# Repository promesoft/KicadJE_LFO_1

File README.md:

# Johansen Engineering KiCadJE_LFO_1.2 (Rev B)

Analogue LFO - minor adjustments - new jacks (PJ321 -> pj324) - remove Sine Adj

555 Based LFO - minor adjustments - new jacks (PJ321 -> pj324) - remove XXX

NAND - Footprint adj

# Purpose
Fix issues with RevA

## 555 LFO
+/- 10V LFO Square, Triangle, Sine

2 frequency ranges

## LFO
+/- 10V LFO Square, Triangle, Sine

## NAND
NOT Gate (pull dn) - NAND Gate (both pull up) - AND Gate (both pull up)

0-10V output - CMOS input

## D-Flip Flop
0-10V output - CMOS input

## MMX
+-10V Input/output - DC couple

Top - 3 input mixer with phase reversal

Bottom - 3 mult output with phase reversal - uses mixer output as input if not applied to mult input

# Status - In the mail
## Initial 
| Stage  | Detail | Status |
| ------------- | ------------- | ------------- |
| create material  | sch/pcb | OK  |
| | gerber | OK |
| production  |   | OK |
|  | produced | Yes |
|  | delivered | OK |

## Preliminary validation
| Test  | Detail | Status |
| ------------- | ------------- | ------------- |
| Initial Inspection | | OK |
| Initial Technical Test | LFO555 |  |
| | | PJ321 should be 1 mm further from the front, center tap works - minor footprint twist in pj324|
| Initial Technical Test | NAND |  |
| | | cut power plane and add 20k across to fix not blowing other units due to hard pull up on tip.
| Initial Product Test | LFO |  |
| Initial Product Test | LFO555 | Sine and Tri not working - needs ac coupling from square - needs dc compensation |
| Initial Product Test | MMX2 |   |
| Initial Product Test | NAND | Now working with 4093 - needs pull up resistors and I/O protection |
| Initial Product Test | FlipFlop |  |

## Secondary validation
| Test  | Detail | Status |
| ------------- | ------------- |------------- |
| Product Test | LFO | |
| Product Test | LFO555 | working right - tri and sine needs tweaking of waveforms |
| Product Test | MMX2 |  |
| Product Test | NAND | working - see issues |
| Product Test | FlipFlop | Working as intended except for LED's |
| Quality | LFO | |
| Quality | LFO555 | |
| Quality | MMX2 | |
| Quality | NAND |  |
| Quality | FlipFlop | |
| Long Term Product Test |  |  |
| Power Draw |  | 

## Errata
### Errata - LFO

### Errata - LFO555

### Errata - MMX2

### Errata - Flip-Flop

### Errata - NAND
Hard pull up to 12 can fry other units !!! Add resistor pull up

Output protection (series resistor?)

## Issues and Notes
### LFO

### 555 LFO
AC coupling of Square should be considered - internal and at least DC adj external

bias current compensation (eg. 10k to GND)

### Flip-Flop

### MMX2
### NAND

# Pictures
## MMX2

------------------------------------------------
# Johansen Engineering KiCadJE_LFO_1
Initial Analogue LFO

# Purpose

# Status - Evaluated
## Initial 
| Stage  | Detail | Status |
| ------------- | ------------- | ------------- |
| create material  | sch/pcb | OK  |
| | gerber | OK |
| production  |   | OK |
|  | produced | Yes |
|  | delivered | Yes |
## Preliminary validation
| Test  | Detail | Status |
| ------------- | ------------- | ------------- |
| Initial Inspection | | OK |
| Initial Technical Test | LFO555 | 555 and 072 gets warm in certain settings |
| Initial Product Test | LFO | Works well with R311 not mounted |
| | | Pot's should be 1 mm closer to front (or jacks further back)|
| Initial Product Test | LFO555 | Sine and Tri not working - RV101B should have 500R series resistor |
| Initial Product Test | MMX2 | Works nicely |
| Initial Product Test | NAND | Not working with 4093 - footprint matches 74HC00 |
| Initial Product Test | FlipFlop | Working |

## Secondary validation
| Test  | Detail | Status |
| ------------- | ------------- |------------- |
| Product Test | LFO | |
| Product Test | LFO555 | not working right |
| Product Test | MMX2 | Working as intended |
| Product Test | NAND | Will Never work |
| Product Test | FlipFlop | Working as intended except for LED's |
| Quality | LFO | Sounds nice - a few constraints on pot's would be nice|
| Quality | LFO555 | |
| Quality | MMX2 | |
| Quality | NAND | Will Never work |
| Quality | FlipFlop | |
| Long Term Product Test |  |  |
| Power Draw |  | 

## Errata
### Errata - LFO555
1 - SW101 too close to P101
### Errata - MMX2
1 - 1206 caps (C201+C202) are too close to the switch to mount both
### Errata - Flip-Flop
1 - LED positions swapped
### Errata - NAND
Will Never work - Footprint wrong so Input is directly coupled to output for some NAND's

## Issues and Notes
### LFO
1 - 100k should not be mounted (it ruins feedback)

2 - Sine pot should have 2k series resistor

3 - C303 could be 100nF and 1uF addon with a switch for high low

4 - Frequency pot is sensitive at low freq

5 - Chose different Jacks

6 - Consider adding series resistor to outputs

7 - mounting holes

8 - Pot's should be 1 mm closer to front (or jacks further back)

### 555 LFO
1 - RV101B should have series resistor (330 - 1k)

2 - All outputs should have a series resistor (470R ?)

3 - Pot's should be 1 mm closer to front (or jacks further back)

4 - RV101 footprint not matching pots

### Flip-Flop
1 - LED positions swapped

### NAND
Will Never work - Footprint wrong so Input is directly coupled to output for some NAND's

# Pictures

# Inspiration from 
https://www.electronics-tutorials.ws/waveforms/555_oscillator.html

http://electro-music.com/forum/topic-31166.html

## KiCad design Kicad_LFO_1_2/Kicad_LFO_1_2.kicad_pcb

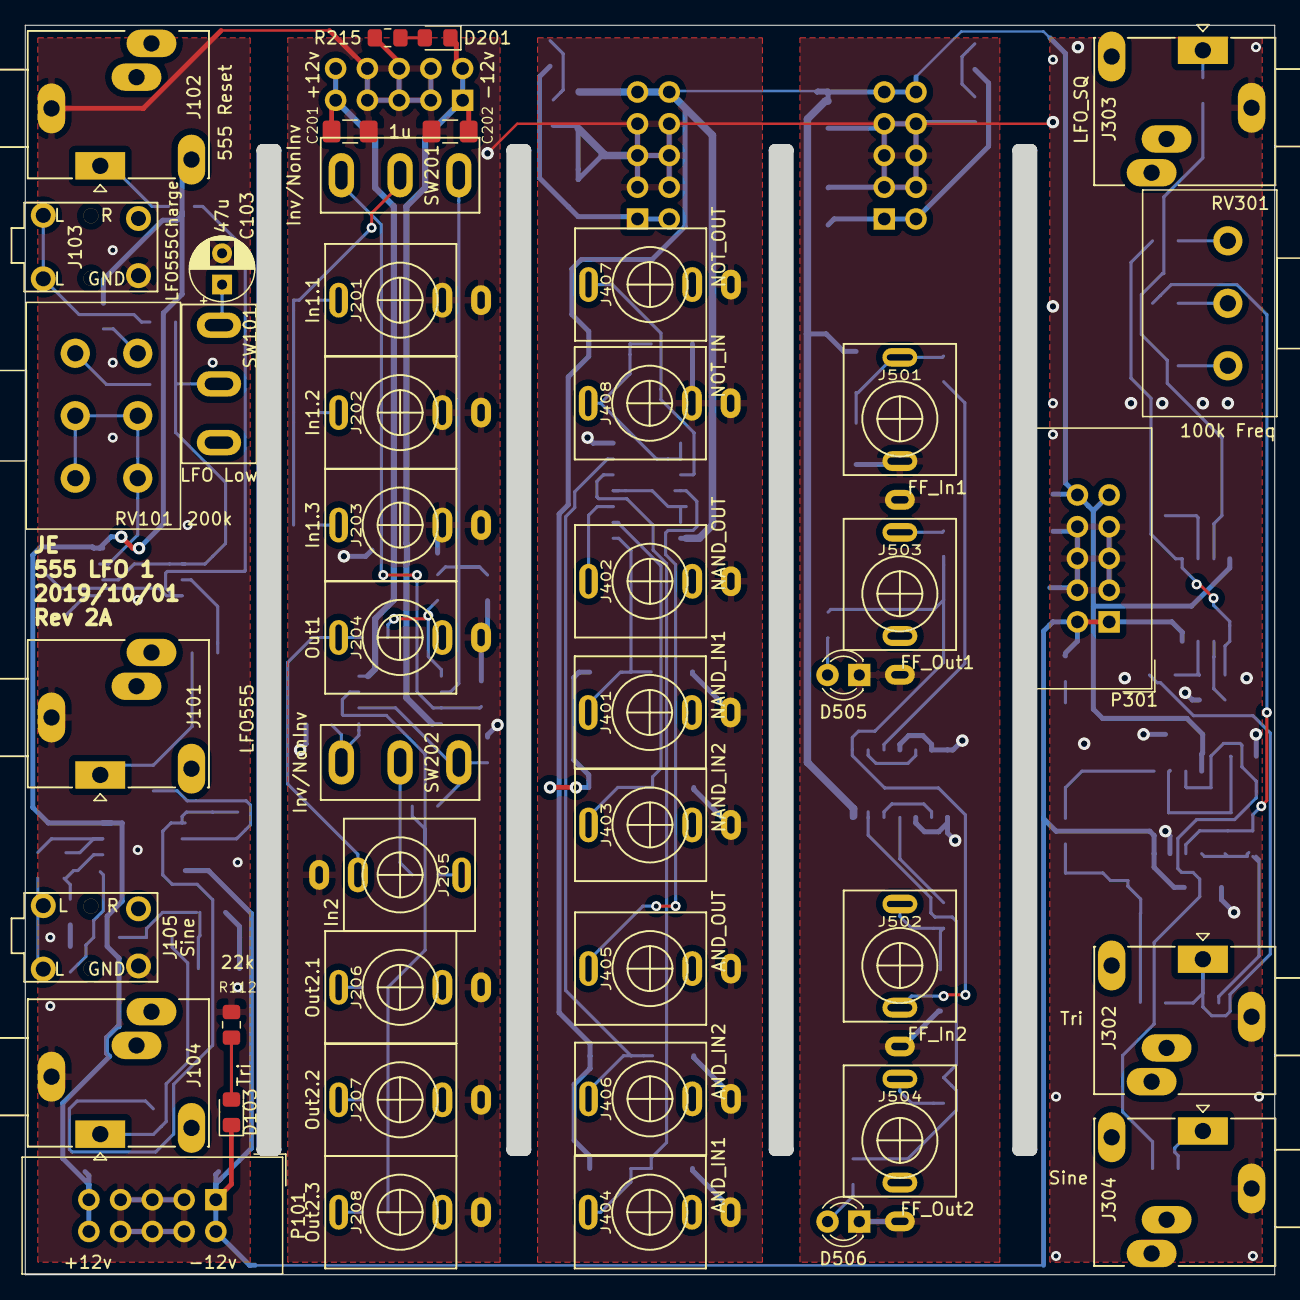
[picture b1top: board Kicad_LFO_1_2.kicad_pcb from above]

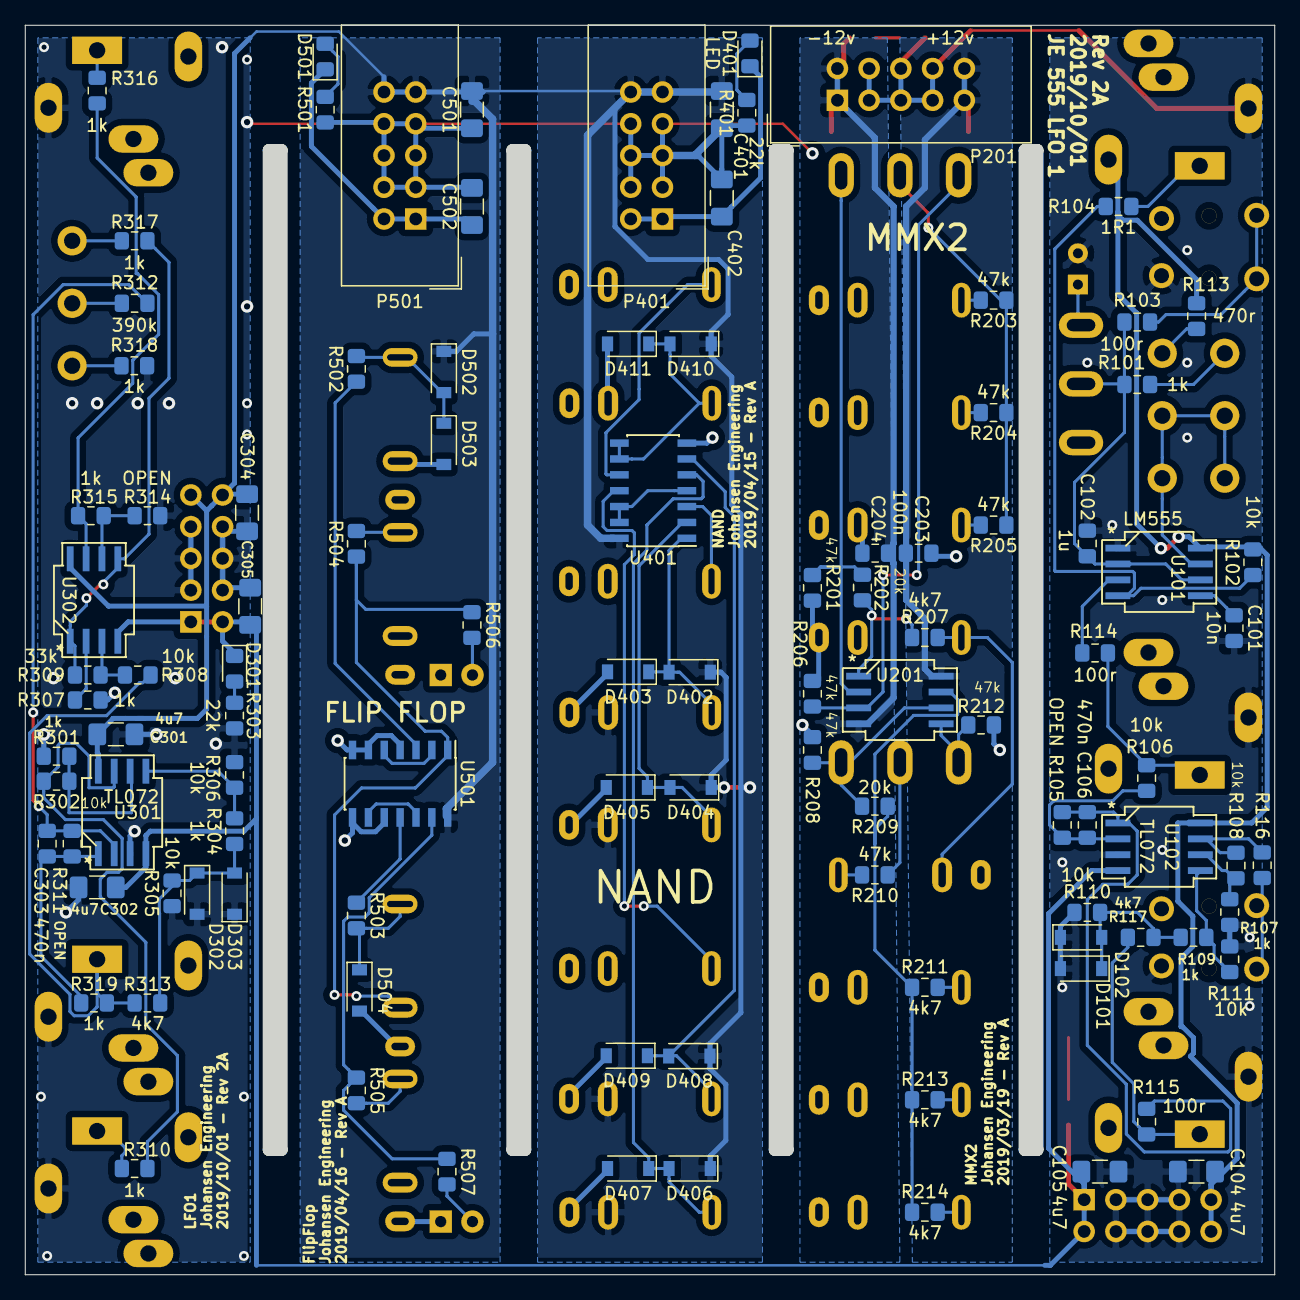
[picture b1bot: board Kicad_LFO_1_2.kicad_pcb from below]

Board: 2 copper layers, 100.0 x 100.0 mm, 147 parts (103 on the bottom side), 83 nets.

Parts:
C101: 10n; C_0805_2012Metric_Pad1.15x1.40mm_HandSolder
C102: 1u; C_0805_2012Metric_Pad1.15x1.40mm_HandSolder
C103: 47u; CP_Radial_D5.0mm_P2.50mm
C104, C105, C301, C302, C401, C402, C501, C502: 4u7; C_1206_3216Metric_Pad1.42x1.75mm_HandSolder
C106, C303: 470n; C_0805_2012Metric_Pad1.15x1.40mm_HandSolder
C201, C202: 1u; C_1206_3216Metric_Pad1.42x1.75mm_HandSolder
C203, C204: 100n; C_0805_2012Metric_Pad1.15x1.40mm_HandSolder
C304, C305: 100n; C_1206_3216Metric_Pad1.42x1.75mm_HandSolder
D101, D102, D302, D303: 1N4148W; D_SOD-123
D103, D201, D301, D401, D501: LED; LED_0805_2012Metric_Pad1.15x1.40mm_HandSolder
D402, D403, D404, D405, D406, D407, D408, D409, D410, D411, D502, D503, D504: MRA4007T3G; D_SOD-123
D505: LEDOut1; LED_D3.0mm
D506: LEDOut2; LED_D3.0mm
J101: LFO555; Jack_3.5mm_Ledino_KB3SPRS_Horizontal
J102: 555 Reset; Jack_3.5mm_Ledino_KB3SPRS_Horizontal
J103: LFO555Charge; AudioJack3StereoNarrow-PJ-321
J104, J302: Tri; Jack_3.5mm_Ledino_KB3SPRS_Horizontal
J105: Sine; AudioJack3StereoNarrow-PJ-321
J201: In1.1; PJ301SM
J202: In1.2; PJ301SM
J203: In1.3; PJ301SM
J204: Out1; PJ301SM
J205: In2; PJ301SM
J206: Out2.1; PJ301SM
J207: Out2.2; PJ301SM
J208: Out2.3; PJ301SM
J303: LFO_SQ; Jack_3.5mm_Ledino_KB3SPRS_Horizontal
J304: Sine; Jack_3.5mm_Ledino_KB3SPRS_Horizontal
J401: NAND_IN1; PJ301SM
J402: NAND_OUT; PJ301SM
J403: NAND_IN2; PJ301SM
J404: AND_IN1; PJ301SM
J405: AND_OUT; PJ301SM
J406: AND_IN2; PJ301SM
J407: NOT_OUT; PJ301SM
J408: NOT_IN; PJ301SM
J501: FF_In1; PJ301SM
J502: FF_In2; PJ301SM
J503: FF_Out1; PJ301SM
J504: FF_Out2; PJ301SM
P101, P201, P301, P401, P501: HEADER_2x5_Doepfer; IDC-Header_2x05_P2.54mm_Vertical
R101, R107, R109, R301, R304, R307, R310, R315, R316, R317, R318, R319: 1k; R_0805_2012Metric_Pad1.15x1.40mm_HandSolder
R102, R106, R108, R110, R111, R302, R305, R306, R308: 10k; R_0805_2012Metric_Pad1.15x1.40mm_HandSolder
R103, R114, R115, R116: 100r; R_0805_2012Metric_Pad1.15x1.40mm_HandSolder
R104: 1R1; R_0805_2012Metric_Pad1.15x1.40mm_HandSolder
R105, R311, R314: OPEN; R_0805_2012Metric_Pad1.15x1.40mm_HandSolder
R112, R215, R303, R401, R501, R506, R507: 22k; R_0805_2012Metric_Pad1.15x1.40mm_HandSolder
R113: 470r; R_0805_2012Metric_Pad1.15x1.40mm_HandSolder
R117, R207, R211, R213, R214, R313, R502, R503, R504, R505: 4k7; R_0805_2012Metric_Pad1.15x1.40mm_HandSolder
R201, R203, R204, R205, R206, R208, R210, R212: 47k; R_0805_2012Metric_Pad1.15x1.40mm_HandSolder
R202, R209: 20k; R_0805_2012Metric_Pad1.15x1.40mm_HandSolder
R309: 33k; R_0805_2012Metric_Pad1.15x1.40mm_HandSolder
R312: 390k; R_0805_2012Metric_Pad1.15x1.40mm_HandSolder
RV101: 200k; Potentiometer_Alps_RK163_Dual_Horizontal
RV301: 100k Freq; Potentiometer_Alps_RK163_Single_Horizontal
SW101: LFO Low; SP1MS1
SW201, SW202: Inv/NonInv; SP1MS1
U101: LM555; AJ_SO-8_5.3x6.2mm_P1.27mm
U102, U301, U302: TL072; AJ_SO-8_5.3x6.2mm_P1.27mm
U201: TL082; AJ_SO-8_5.3x6.2mm_P1.27mm
U401: 4011; SOIC-14_3.9x8.7mm_P1.27mm
U501: 4013; SOIC-14_3.9x8.7mm_P1.27mm

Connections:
+12L: C201.1, C203.1, P201.9, P201.10, U201.8
+12V: C104.2, C301.2, C304.2, C401.2, C501.2, D402.1, D404.1, D406.1, D408.1, D410.1, D502.1, J102.TN, J401.TN, J403.TN, J404.TN, J406.TN, P101.9, P101.10, P301.9, P301.10, P401.9, P401.10, P501.9, P501.10, R102.2, R113.2, U101.8, U102.8, U301.8, U302.8, U401.14, U501.14
-12V: C105.1, C302.1, C305.1, C402.1, C502.1, D103.1, D301.1, D401.1, D501.1, P101.1, P101.2, P301.1, P301.2, P401.1, P401.2, P501.1, P501.2, U102.4, U301.4, U302.4
-12VA: C202.2, C204.2, D201.1, P201.1, P201.2, U201.4
/KicadJE_MMX2/Inv1: R201.1, R202.2, SW201.1, U201.2
/KicadJE_MMX2/Inv2: R208.1, R209.2, SW202.1, U201.6
AND_IN1: D406.2, D407.1, J404.T, U401.5
AND_IN2: D408.2, D409.1, J406.T, U401.6
Charge: J103.T, R103.1
FF_IN1: R502.1, U501.3
FF_IN2: R503.1, U501.11
FF_OUT1: J502.TN, R504.1, R506.1, U501.1
FF_OUT2: R505.1, R507.1, U501.13
GND: C101.2, C102.2, C103.2, C104.1, C105.2, C201.2, C202.1, C203.2, C204.1, C301.1, C302.2, C304.1, C305.2, C401.1, C402.2, C501.1, C502.2, D101.2, D102.1, D302.2, D303.1, D403.2, D405.2, D407.2, D409.2, D411.2, D503.2, D504.2, D505.1, D506.1, J101.S, J102.S, J103.S, J104.S, J105.S, J201.S, J201.TN, J202.S, J202.TN, J203.S, J203.TN, J204.S, J205.S, J206.S, J207.S, J208.S, J302.S, J303.S, J304.S, J401.S, J402.S, J403.S, J404.S, J405.S, J406.S, J407.S, J408.S, J408.TN, J501.S, J501.TN, J502.S, J503.S, J504.S, P101.3, P101.4, P101.5, P101.6, P101.7, P101.8, P201.3, P201.4, P201.5, P201.6, P201.7, P201.8, P301.3, P301.4, P301.5, P301.6, P301.7, P301.8, P401.3, P401.4, P401.5, P401.6, P401.7, P401.8, P501.3, P501.4, P501.5, P501.6, P501.7, P501.8, R107.1, R110.1, R111.1, R112.1, R201.2, R206.1, R208.2, R212.1, R215.1, R301.1, R303.1, R305.1, R306.1, R307.1, R314.1, R318.2, R401.1, R501.1, U101.1, U102.3, U301.3, U401.7, U501.4, U501.6, U501.7, U501.8, U501.10
In1: R203.1, R204.1, R205.1, SW201.2
In2: R210.1, SW202.2
NAND_IN1: D402.2, D403.1, J401.T, U401.1
NAND_IN2: D404.2, D405.1, J403.T, U401.2
NOT_IN: D410.2, D411.1, J408.T, U401.8, U401.9
unnamed: C101.1, U101.5
unnamed: C102.1, R101.2, R103.2, SW101.2, U101.2, U101.6
unnamed: C103.1, SW101.3
unnamed: C106.1, R105.2, R115.2, U102.1
unnamed: C106.2, R105.1, R106.2, U102.2
unnamed: C303.1, R311.2, R319.1, U301.1
unnamed: C303.2, R311.1, R312.2, U301.2
unnamed: D101.1, D102.2, R109.1, R110.2, R117.2
unnamed: D103.2, R112.2
unnamed: D201.2, R215.2
unnamed: D301.2, R303.2
unnamed: D302.1, D303.2, R304.1, R305.2, R313.2
unnamed: D401.2, R401.2
unnamed: D501.2, R501.2
unnamed: D502.2, D503.1, J501.T, R502.2
unnamed: D504.1, J502.T, R503.2
unnamed: D505.2, R506.2
unnamed: D506.2, R507.2
unnamed: J201.T, R203.2
unnamed: J202.T, R204.2
unnamed: J203.T, R205.2
unnamed: J204.T, J205.TN, R207.2
unnamed: J205.T, R210.2
unnamed: J206.T, R211.2
unnamed: J207.T, R213.2
unnamed: J208.T, R214.2
unnamed: J402.T, U401.3
unnamed: J405.T, U401.11
unnamed: J407.T, U401.10
unnamed: J503.T, R504.2
unnamed: J504.T, R505.2
unnamed: R101.1, RV101.1
unnamed: R102.1, R104.1, U101.4
unnamed: R107.2, R108.1, U102.6
unnamed: R108.2, R116.2, U102.7
unnamed: R109.2, R111.2, U102.5
unnamed: R113.1, RV101.4
unnamed: R114.2, U101.3
unnamed: R206.2, SW201.3, U201.3
unnamed: R212.2, SW202.3, U201.5
unnamed: R301.2, R302.1, U301.6
unnamed: R302.2, R310.1, U301.7
unnamed: R304.2, R306.2, U301.5
unnamed: R307.2, U302.2
unnamed: R308.2, R309.1, U302.3
unnamed: R309.2, R317.1, U302.1, U302.5
unnamed: R314.2, R315.1, U302.6
unnamed: R315.2, R316.1, U302.7
unnamed: R317.2, RV301.3
unnamed: R318.1, RV301.1
unnamed: RV101.2, RV101.3, RV101.5, RV101.6, U101.7
unnamed: U401.4, U401.12, U401.13
unnamed: U501.2, U501.5
unnamed: U501.9, U501.12
Out1: R202.1, R207.1, U201.1
Out2: R209.1, R211.1, R213.1, R214.1, U201.7
Reset: J102.T, R104.2
Sine: J105.T, R116.1
Sine3: J304.T, R310.2
Square: J101.T, R106.1, R114.1
Square3: J303.T, R316.2
Square3fb: R312.1, RV301.2
Tri: J104.T, R115.1, R117.1
Tri3: J302.T, R308.1, R313.1, R319.2

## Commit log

2019-03-16 Inspiration and upd SCH 555
2019-03-18 Init PCB
2019-03-18 Op amp and IDC power
2019-03-18 Sine and tri integrator added
2019-03-18 Update Kicad_LFO_1.sch
    footprints and caps
2019-03-18 Update fp-info-cache
2019-03-19 Routed 555 LFO
2019-03-19 Update Kicad_LFO_1.kicad_pcb
    3D
2019-03-19 PCB bottom layer Vcc
2019-03-19 Power LED and MMX2
2019-03-19 sheet naming
2019-03-19 2x GND on MMX2
2019-03-19 Power settings + Inv net
2019-03-19 cleanup and decoupl
2019-03-19 Logo - again
2019-03-19 MMX2 upd
2019-03-20 OpAmp LFO added
2019-03-21 TL072 LFO on PCB
2019-03-22 MMX2
2019-04-15 MMX_NAND
2019-04-15 Naming
2019-04-15 Diode protection
2019-04-15 U401 remove
2019-04-15 OpAmp LFO components placed
2019-04-16 FF Sch done 1
2019-04-16 Protection
2019-04-16 Annotate
    Annotate
2019-04-16 THT Placed
2019-04-16 LED Out
2019-04-16 SMD Placed
2019-04-16 Copper plane
2019-04-16 gerber
2019-04-22 BOM created
2019-04-22 NAND/AND TN to +12V default
    to enable buffer/inverter mode with only one input
2019-04-22 RevB PCB
2019-06-03 Pict
2019-06-03 Second edition prepared
2019-06-03 LED's swapped for flip flop
2019-10-01 Fixing Errata from rev 1B
2019-10-01 Fixing LFO Errata
2019-10-01 Jack footprints changed to Connector_Audio:Jack_3.5mm_Ledino_KB3SPRS_Horizontal
2019-10-01 Annotate Rev 2A
2019-10-01 footprint adj Rev 2A
2019-10-01 LFO 1 Routed and labeled
2019-10-01 Jack PJ321 for some
2019-10-01 LFO 555 done
2019-10-02 Jack footprint
2019-10-02 Rev_2A_Gerber
2020-02-15 rev 1.3
2020-02-16 NAND - resistor out
2020-02-16 LFO AC Couple Square
2020-02-16 FF - Fix LED dimm issue
2020-02-16 Update KicadJE_NAND.sch
    Pull up +12V added resistors to avoid burning outputs upon connection
2020-02-17 nand sch
2020-03-17 MMX sch
